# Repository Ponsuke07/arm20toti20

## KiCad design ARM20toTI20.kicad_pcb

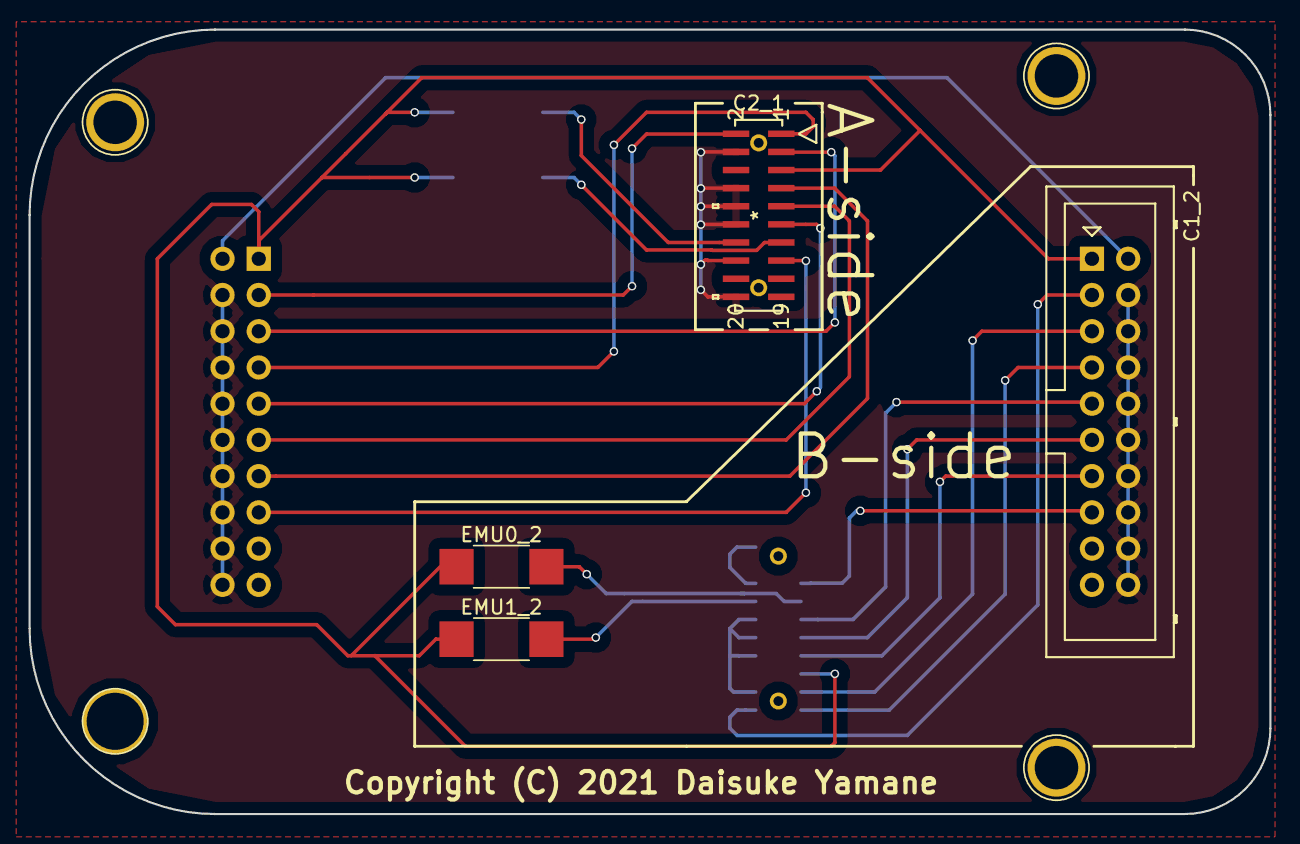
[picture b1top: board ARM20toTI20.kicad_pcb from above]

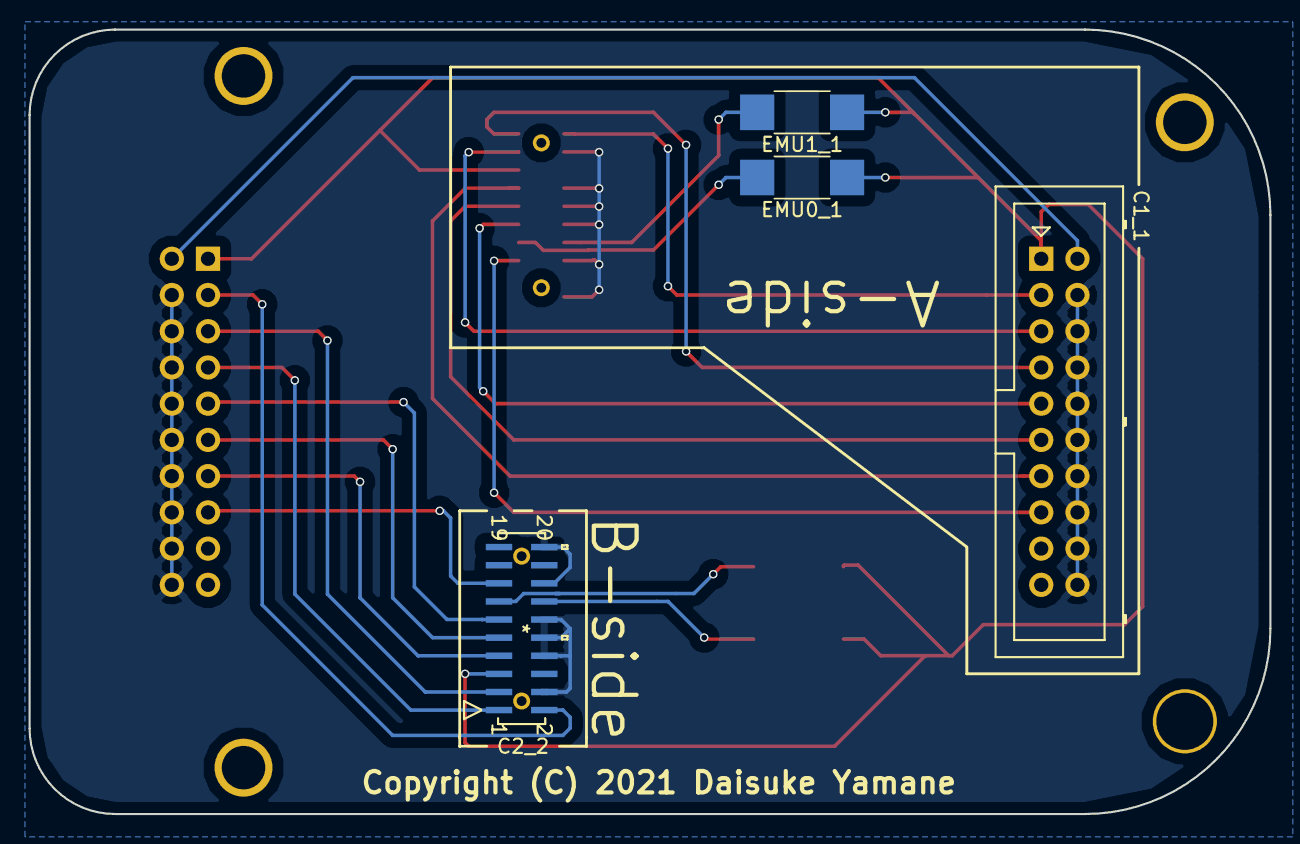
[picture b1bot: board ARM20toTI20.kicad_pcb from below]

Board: 2 copper layers, 87.0 x 55.0 mm, 12 parts (4 on the bottom side), 18 nets.

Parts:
C1_1, C1_2: ARM20JTAG; Multicomp_MC9A12-2034_2x10x2.54mm_Straight
C2_1, C2_2: TI20JTAG; CLP-110-02-F-D-K
EMU0_1, EMU0_2, EMU1_1, EMU1_2: -; R_2010_HandSoldering
w1, w2, w3, w4: 1pin

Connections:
GND: C1_1.4, C1_1.6, C1_1.8, C1_1.10, C1_1.12, C1_1.14, C1_1.16, C1_1.18, C1_1.20, C1_2.4, C1_2.6, C1_2.8, C1_2.10, C1_2.12, C1_2.14, C1_2.16, C1_2.18, C1_2.20, C2_1.4, C2_1.8, C2_1.10, C2_1.12, C2_1.16, C2_1.20, C2_2.4, C2_2.8, C2_2.10, C2_2.12, C2_2.16, C2_2.20
unnamed: C1_1.2, C1_2.2
unnamed: C1_1.3, C1_2.3, C2_1.2, C2_2.2
unnamed: C1_1.5, C1_2.5, C2_1.3, C2_2.3
unnamed: C1_1.7, C1_2.7, C2_1.1, C2_2.1
unnamed: C1_1.9, C1_2.9, C2_1.11, C2_2.11
unnamed: C1_1.11, C1_2.11, C2_1.9, C2_2.9
unnamed: C1_1.13, C1_2.13, C2_1.7, C2_2.7
unnamed: C1_1.15, C1_2.15, C2_1.15, C2_2.15
unnamed: C1_1.17, C1_2.17
unnamed: C1_1.19, C1_2.19
unnamed: C2_1.6, C2_2.6
unnamed: C2_1.13, C2_2.13, EMU0_1.2, EMU0_2.2
unnamed: C2_1.14, C2_2.14, EMU1_1.2, EMU1_2.2
unnamed: C2_1.17, C2_2.17
unnamed: C2_1.18, C2_2.18
unnamed: C2_1.19, C2_2.19
VDD: C1_1.1, C1_2.1, C2_1.5, C2_2.5, EMU0_1.1, EMU0_2.1, EMU1_1.1, EMU1_2.1

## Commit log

2020-05-29 Add gitignore
2021-02-21 Add mit license
2021-02-21 v0.0.1

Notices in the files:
ARM20toTI20.kicad_pcb:
Copyright (C) 2021 Daisuke Yamane
